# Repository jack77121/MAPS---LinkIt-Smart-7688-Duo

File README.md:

# Micro Air Pollution Sensing

MAPS v5.1 appearance

## Story
**M**icro **A**ir **P**ollution **S**ensing - MAPS

Air pollution is a hot topic in recent years, especially - **Particulate Matter**. Traditional sensing method, we can only depend on professional sensors/devices, with large volume, heave weight and insanity price.
Thanks to the technology, now we could build our own air pollution sensing station, with micro volume, light weight and the price is affordable :). With MAPS, you can sense air pollution any where, any time by yourself, you can also give it a battery module to increase its mobility!

For more air pollution sensing project, you can visit [LASS facebook](https://www.facebook.com/groups/1607718702812067/) and [LASS github](https://github.com/LinkItONEDevGroup/LASS), we are makers who sense anything in our environment!

## Hardware & Sensors
Module     			 |	Description
---------------------|--------------
LinkIt Smart 7688 Duo|Mainboard
G5 (pms5003)			 |Particalute matter (PM)
BME280       			 |Temperature, humidity & Air pressure
SHT25					 |Temperature & humidity (optional)

p.s SHT25 is for device temperature, humidity monitoring and future calibration usage, MAPS is be still full functional without it.

## PCB layout & dimensions

(unit: mm)

## Installing
### Instrution
MAPS use both MT7688AN (MPU) and ATmega32U4 (MCU) onboard to complete its jobs. They communicate through UART (in this project). 

ATmega32U4 is reponsible for sensors data collection.( and data boardcasting through LPWAN, if you use LoRa.)

There is an OpenWrt Linux OS running on 7688 duo, so MT7688AN is capable for multiple jobs, its main task is data publishing through MQTT to the backend server, others like time sync, program update OTA and user preference setting (wifi, manual GPS) are its routine.

Installation will have two parts, first part is about the MCU program (arduino), and second part are the scripts for MPU.

p.s scripts for MPU are still in progress, will be update ASAP.

Below is the installing instruction about 
### MCU program (arduino)
1. You can download Arduino IDE [here](https://www.arduino.cc/en/Main/Software).
2. Put all folders in `library` into your arduino `libraries` folder. [Tutorial](https://www.arduino.cc/en/Guide/Libraries#toc5)
3. Use Arduino IDE to upload the code: `linkit_7688_duo_lora.ino`. [Tutorial](https://www.arduino.cc/en/Guide/HowtoUpload)

p.s `linkit_7688_duo_lora.ino` need to be in a same name folder, in this project, called `linkit_7688_duo_lora`. If you don't do let, the Arduino app will still ask you to make one. 

### MPU scripts (python + ash)
(Continue updating...)

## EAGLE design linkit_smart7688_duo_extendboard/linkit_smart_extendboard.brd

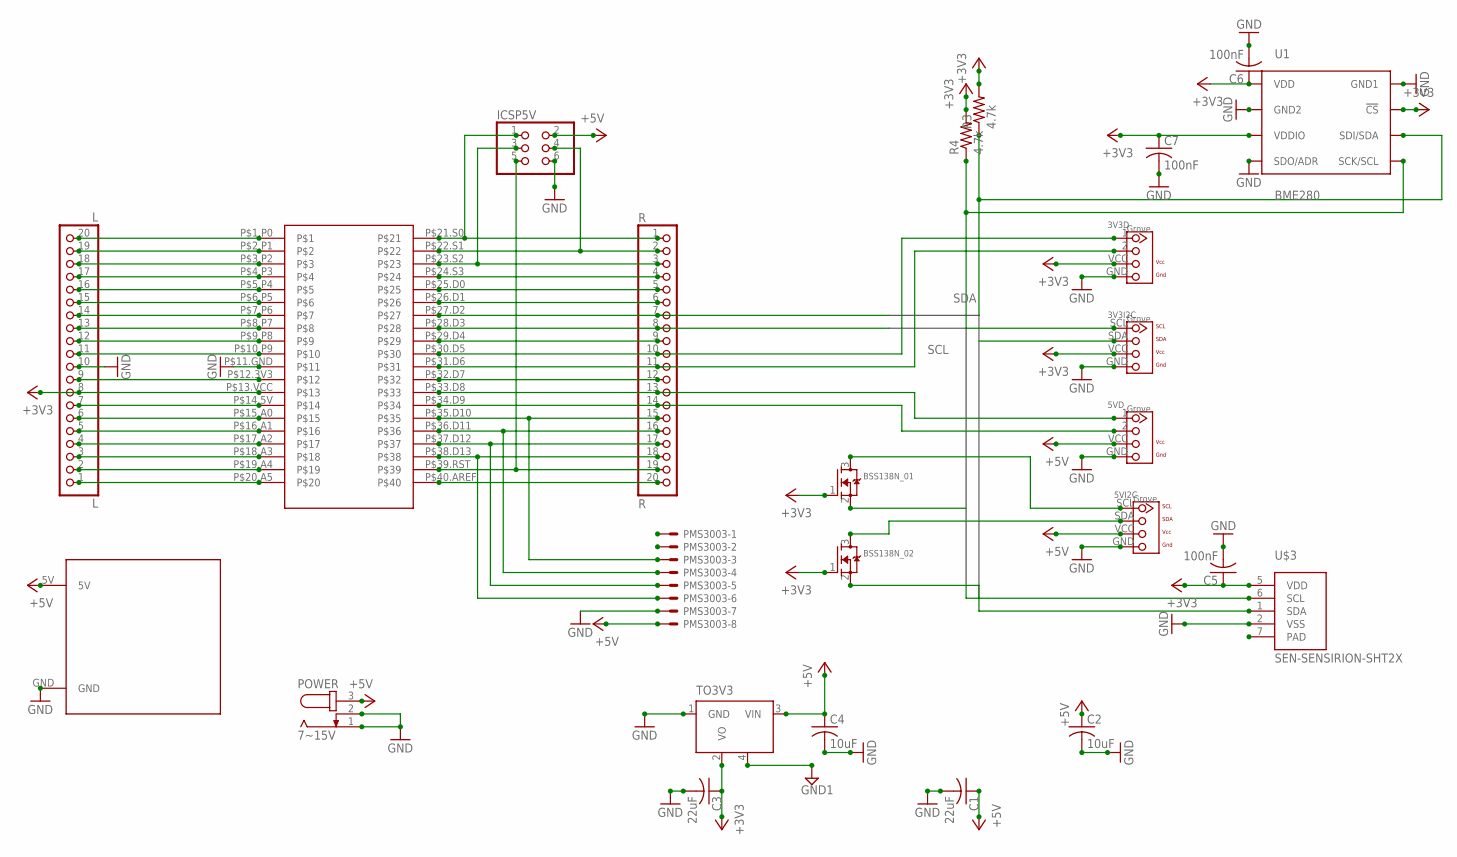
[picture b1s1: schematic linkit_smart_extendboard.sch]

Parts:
3V3D, 3V3I2C, 5VD, 5VI2C: TWIG-4P-2.0-2.0; 4P-2.0
BSS138N_01, BSS138N_02: MOSFET-NWAVE; SOT23-W
C1, C3: 22uF; C0805K
C2, C4: 10uF; C0805K
C5, C6, C7: 100nF; C0805K
ICSP5V: PINHD-2X3; 2X03
L: L; 1X20-BIG
PMS3003: 53047-08
POWER: 7~15V; SPC4077
R: R; 1X20-BIG
R3, R4: 4.7k; R0805
TO3V3: LM2936MP-3.0; SOT223
U1: BME280; BME280_LGA
U$1: LINKIT7688
U$3: SEN-SENSIRION-SHT2X
U$4: PIN2MM

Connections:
+3V3: 3V3D.VCC (3), 3V3I2C.VCC (3), BSS138N_01.1 (G), BSS138N_02.1 (G), C3.1, C5.1, C6.1, C7.1, L.8, R3.2, R4.2, TO3V3.2 (VO), U1.P$2 (!CS), U1.P$6 (VDDIO), U1.P$8 (VDD), U$1.P$13.VCC, U$3.5 (VDD)
+5V: 5VD.VCC (3), 5VI2C.VCC (3), C1.1, C2.1, C4.1, ICSP5V.2, PMS3003.8, POWER.3, TO3V3.3 (VIN), U$4.5V
GND: 3V3D.GND (4), 3V3I2C.GND (4), 5VD.GND (4), 5VI2C.GND (4), C1.2, C2.2, C3.2, C4.2, C5.2, C6.2, C7.2, ICSP5V.6, L.10, PMS3003.7, POWER.1, POWER.2, TO3V3.1 (GND), U1.P$1 (GND1), U1.P$5 (SDO/ADR), U1.P$7 (GND2), U$1.P$11.GND, U$3.2 (VSS), U$4.GND
GND1: TO3V3.4 (HS)
unnamed: L.9, U$1.P$12.3V3
unnamed: PMS3003.3, R.15, U$1.P$35.D10
unnamed: L.7, U$1.P$14.5V
unnamed: L.6, U$1.P$15.A0
unnamed: L.5, U$1.P$16.A1
unnamed: L.4, U$1.P$17.A2
unnamed: L.3, U$1.P$18.A3
unnamed: L.2, U$1.P$19.A4
unnamed: L.1, U$1.P$20.A5
unnamed: 3V3D.1, R.10, U$1.P$30.D5
unnamed: L.19, U$1.P$2.P1
unnamed: L.18, U$1.P$3.P2
unnamed: L.17, U$1.P$4.P3
unnamed: L.16, U$1.P$5.P4
unnamed: L.15, U$1.P$6.P5
unnamed: L.14, U$1.P$7.P6
unnamed: L.13, U$1.P$8.P7
unnamed: L.12, U$1.P$9.P8
unnamed: L.11, U$1.P$10.P9
unnamed: L.20, U$1.P$1.P0
unnamed: ICSP5V.1, R.1, U$1.P$21.S0
unnamed: ICSP5V.4, R.2, U$1.P$22.S1
unnamed: ICSP5V.3, R.3, U$1.P$23.S2
unnamed: R.4, U$1.P$24.S3
unnamed: R.5, U$1.P$25.D0
unnamed: R.6, U$1.P$26.D1
unnamed: R.9, U$1.P$29.D4
unnamed: R.12, U$1.P$32.D7
unnamed: PMS3003.4, R.16, U$1.P$36.D11
unnamed: 5VD.2, R.14, U$1.P$34.D9
unnamed: 3V3D.2, R.11, U$1.P$31.D6
unnamed: 5VD.1, R.13, U$1.P$33.D8
unnamed: ICSP5V.5, R.19, U$1.P$39.RST
unnamed: PMS3003.6, R.18, U$1.P$38.D13
unnamed: 5VI2C.SCL (1), BSS138N_01.3 (D)
unnamed: R.20, U$1.P$40.AREF
unnamed: PMS3003.5, R.17, U$1.P$37.D12
unnamed: 5VI2C.SDA (2), BSS138N_02.3 (D)
SCL: 3V3I2C.SCL (1), BSS138N_01.2 (S), R.8, R4.1, U1.P$4 (SCK/SCL), U$1.P$28.D3, U$3.6 (SCL)
SDA: 3V3I2C.SDA (2), BSS138N_02.2 (S), R.7, R3.1, U1.P$3 (SDI/SDA), U$1.P$27.D2, U$3.1 (SDA)

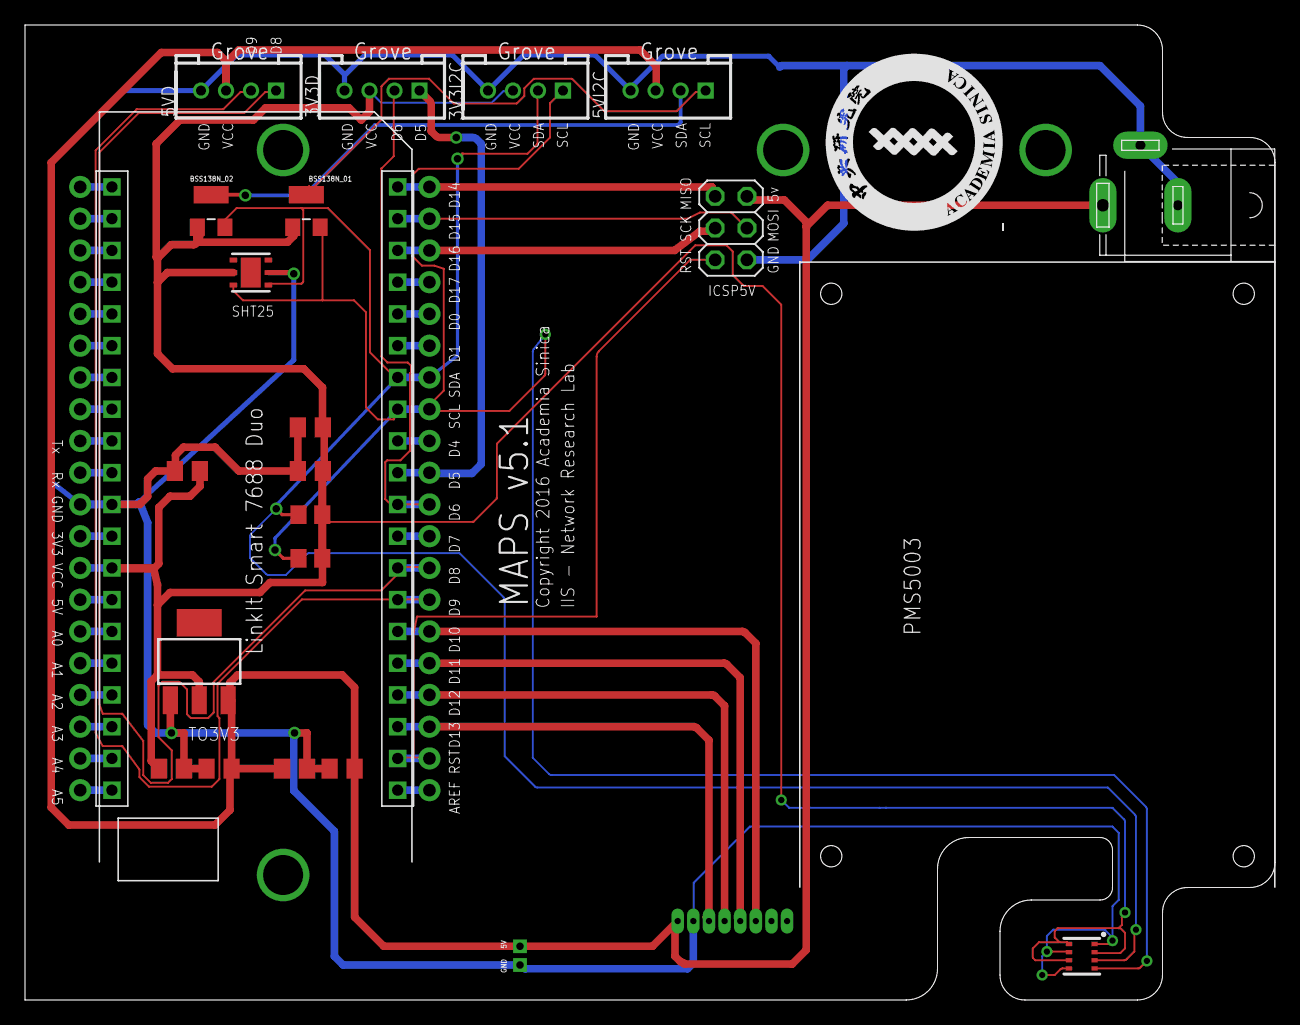
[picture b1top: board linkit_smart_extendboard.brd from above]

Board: 2 copper layers, 100.0 x 78.0 mm, 26 parts (0 on the bottom side), 43 nets.

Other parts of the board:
U$2: G5

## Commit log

2016-09-02 init commit
2016-09-02 add PCB layout image
2016-09-12 add GPS module
2016-09-12 add eagle PCB files
2016-09-12 add GPS_FOX1 library
2016-09-12 avoid most of the 90 degree circuit layout
2016-09-13 reduce most of 90 degree circuit layout
2016-09-13 rm temp file
2016-09-21 for demo, hide SHT value from display on OLED & disable GPS module
2016-09-21 update readme & upload appearance figure
2016-09-21 update appearance
2016-09-21 update figure name
2016-09-21 update figure
2016-09-24 revision PCB layout
2016-09-26 update pcb layout
2016-09-29 update PCB layout,prepare for future box design
2016-10-03 modify PCB layout to fit the RP1135C box and add RP1135C drafting pdf
2016-10-04 update PCB layout for RP1135C box
2016-10-05 update PCB layout & RP1135C piercing 3D design
2016-10-06 export RP1135C STL
2016-10-07 change BME280 position to another side, flip the G5 and change position, change DC position
2016-10-12 RP1135C 3D design box only
2016-10-18 add gitignore
2016-10-18 add gitignore, update eagle PCB
2016-10-19 add dimension in 3dm, remove 5v LDO on .brd & sch .file we don't need them any more, because the DC in is already 5v
2016-10-26 push data from arduino to MT7688, and use wifi send MQTT package to the broker
2016-11-01 update G5 checksum & RP1135C box design (more hole for BME280)
2016-11-02 update ignore file
2016-11-04 upgrade coding format...still on going...
2016-11-07 change arduino code format, update screw hole size for G5 on PCB
2016-11-25 update arduino code format
2016-12-02 update arduino code, data string to MCU
2016-12-30 update board-pdf, png, arduino code
2016-12-30 update arduino code
2017-01-02 update README, and figures
2017-01-03 update gitignore
2017-01-03 remore .DS_Store
2017-01-11 add newline for string which push to MT7688, for fixing bug that serial readline() might read more than once
2017-02-05 add user guide
2017-02-05 add MAPS_user_guide.pages to gitignore
2017-02-05 rm user guide.pages
2017-02-05 update user guide
2017-02-05 add user guide.pages
2017-02-13 add user guide_TW, update user guide
2017-04-19 user guide, ignore files
2017-04-19 refresh git cache
2017-04-19 update format
2017-06-12 add sinica logo on PCB

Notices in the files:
linkit_smart7688_duo_extendboard/linkit_smart_extendboard.brd:
Copyright 2016 Academia Sinica
